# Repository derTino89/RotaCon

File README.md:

# RotaCon
 full Project with 3D-Print, PCB-Layouts, Arduino-Program etc.

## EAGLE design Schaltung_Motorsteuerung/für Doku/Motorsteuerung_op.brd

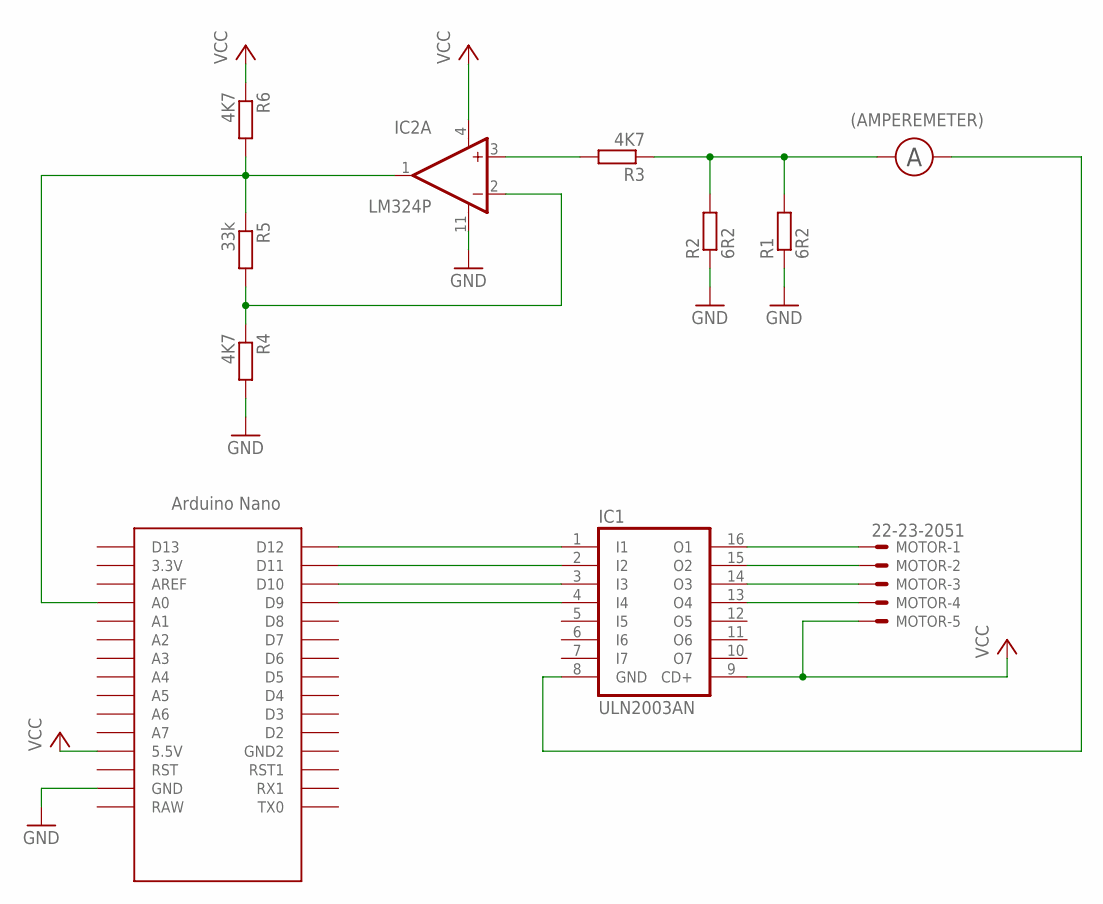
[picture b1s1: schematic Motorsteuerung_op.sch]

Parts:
IC1: ULN2003AN; DIL16
IC2: LM324P; DIL14
MOTOR: 22-23-2051
R1, R2: 6R2; 0207/10
R3, R4, R6: 4K7; 0207/10
R5: 33k; 0207/10
U$1: NANO

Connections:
GND: IC2.11 (V-), R1.1, R2.1, R4.2, U$1.GND
unnamed: IC1.16 (O1), MOTOR.1
unnamed: IC1.1 (I1), U$1.D12
unnamed: IC1.2 (I2), U$1.D11
unnamed: IC1.3 (I3), U$1.D10
unnamed: IC1.4 (I4), U$1.D9
unnamed: IC1.15 (O2), MOTOR.2
unnamed: IC1.14 (O3), MOTOR.3
unnamed: IC1.13 (O4), MOTOR.4
unnamed: R1.2, R2.2, R3.1
unnamed: IC2.3 (+IN), R3.2
unnamed: IC2.1 (OUT), R5.1, R6.2, U$1.A0
unnamed: IC2.2 (-IN), R4.1, R5.2
VCC: IC1.9 (CD+), IC2.4 (V+), MOTOR.5, R6.1, U$1.5V (5.5V)

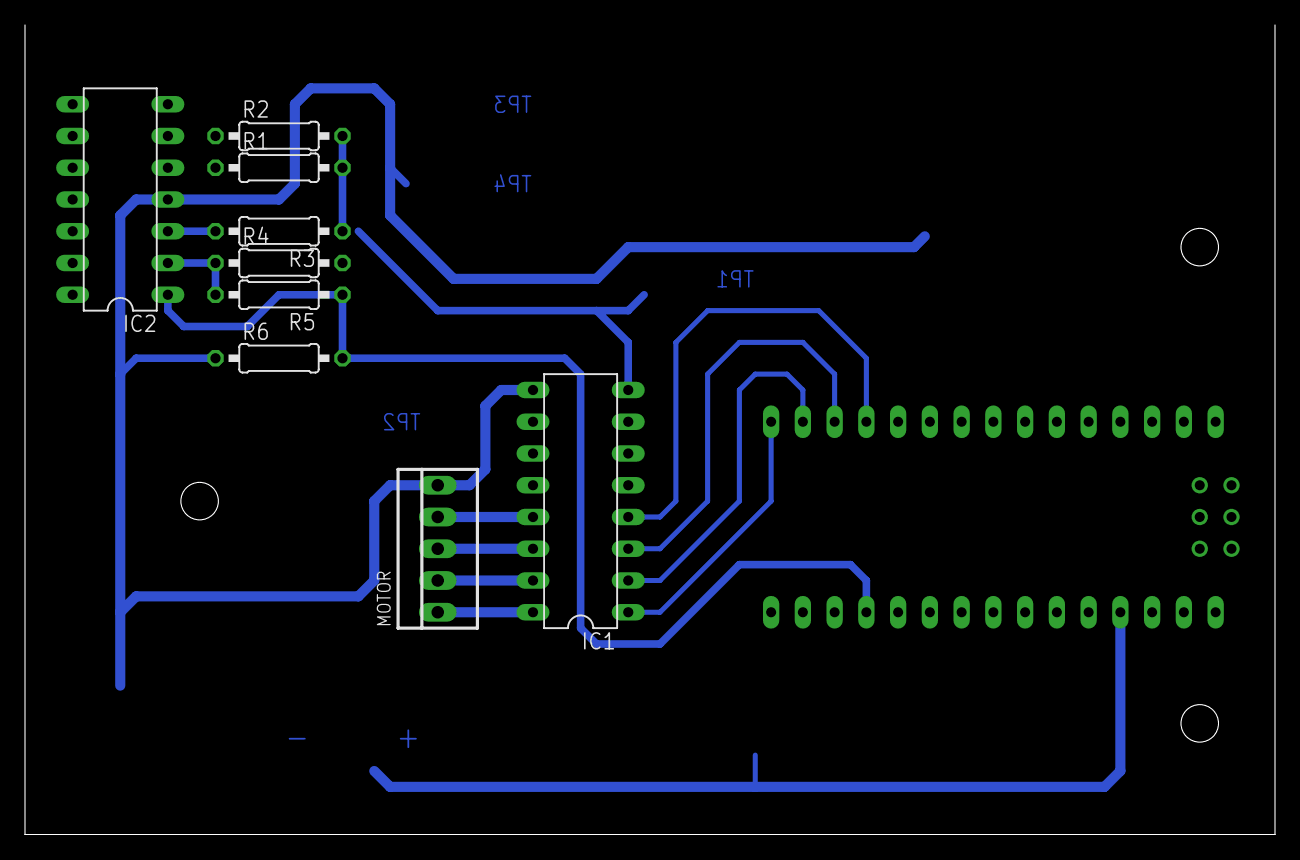
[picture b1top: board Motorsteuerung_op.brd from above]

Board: 2 copper layers, 100.0 x 64.8 mm, 10 parts (0 on the bottom side), 14 nets.

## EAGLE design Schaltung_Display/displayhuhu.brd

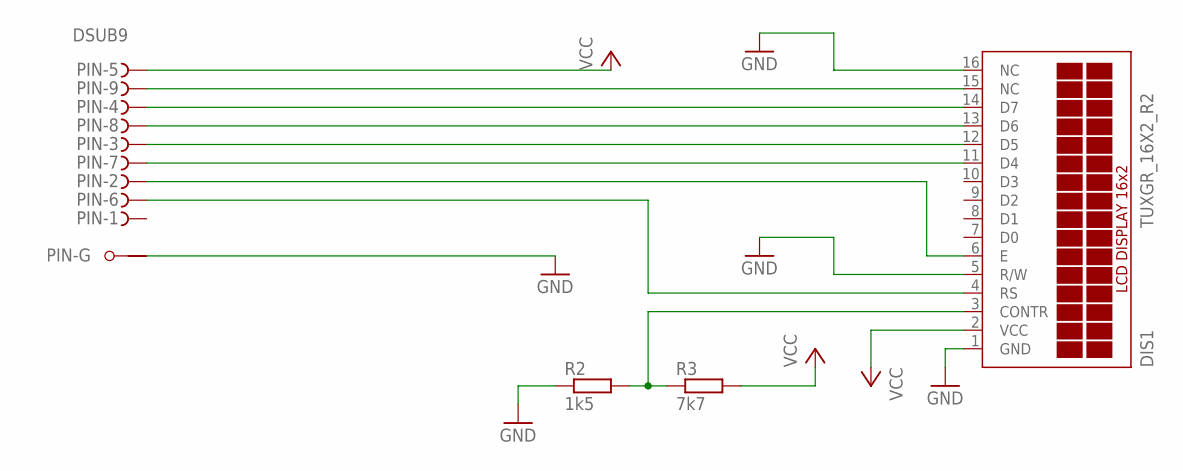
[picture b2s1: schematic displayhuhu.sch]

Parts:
DIS1: TUXGR_16X2_R2
PIN: DSUB9; F09HP
R2: 1k5; 0207/10
R3: 7k7; 0207/10

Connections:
GND: DIS1.1 (GND), DIS1.5 (R/W), DIS1.16 (NC), PIN.G1, R2.1
unnamed: DIS1.6 (E), PIN.2 (F)
unnamed: DIS1.11 (D4), PIN.7 (F)
unnamed: DIS1.12 (D5), PIN.3 (F)
unnamed: DIS1.13 (D6), PIN.8 (F)
unnamed: DIS1.14 (D7), PIN.4 (F)
unnamed: DIS1.15 (NC), PIN.9 (F)
unnamed: DIS1.4 (RS), PIN.6 (F)
unnamed: DIS1.3 (CONTR), R2.2, R3.1
VCC: DIS1.2 (VCC), PIN.5 (F), R3.2

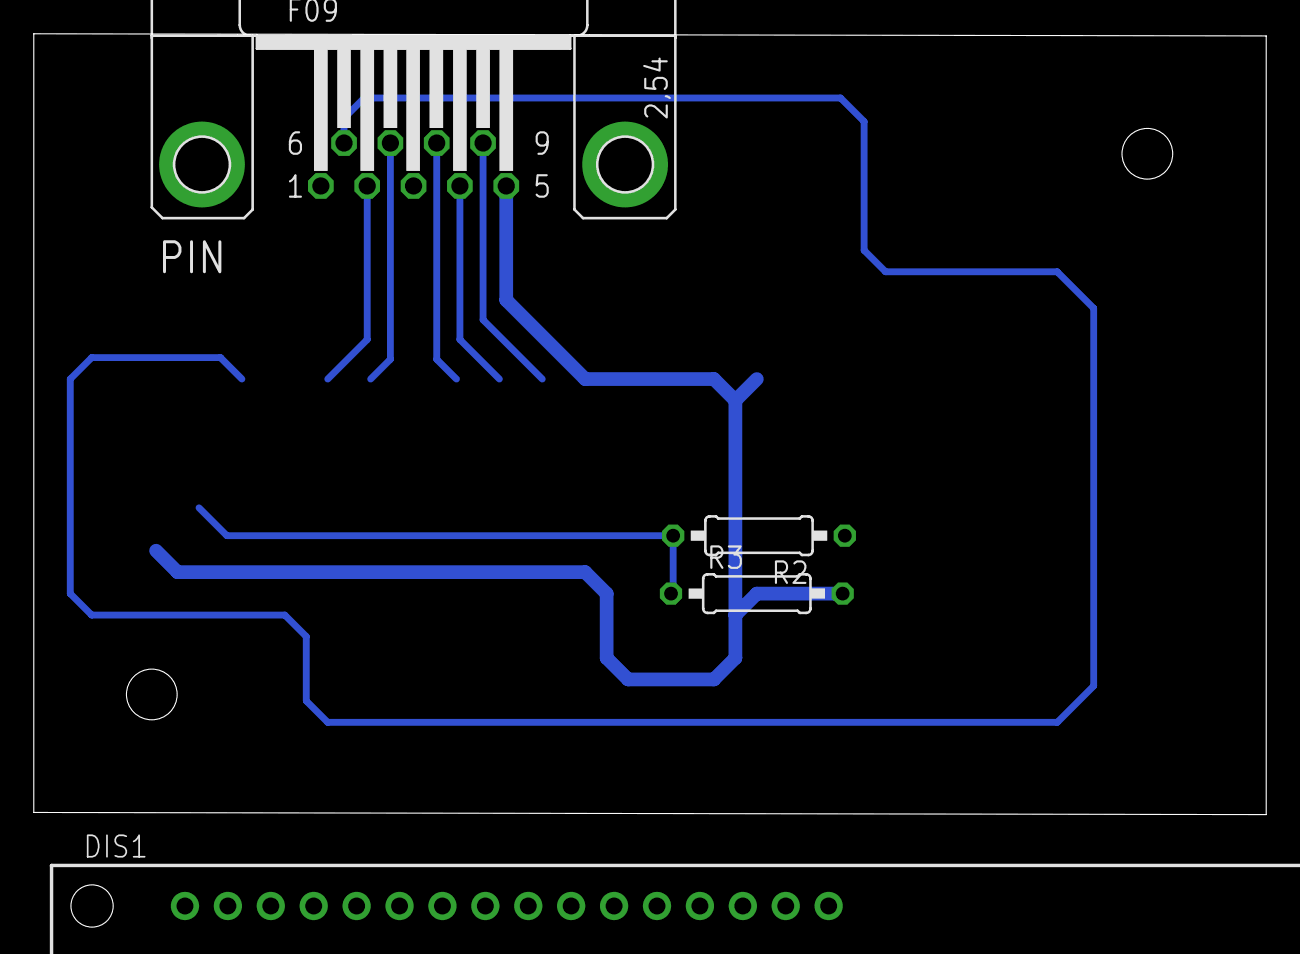
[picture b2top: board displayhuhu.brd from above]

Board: 2 copper layers, 72.9 x 46.2 mm, 4 parts (0 on the bottom side), 10 nets.

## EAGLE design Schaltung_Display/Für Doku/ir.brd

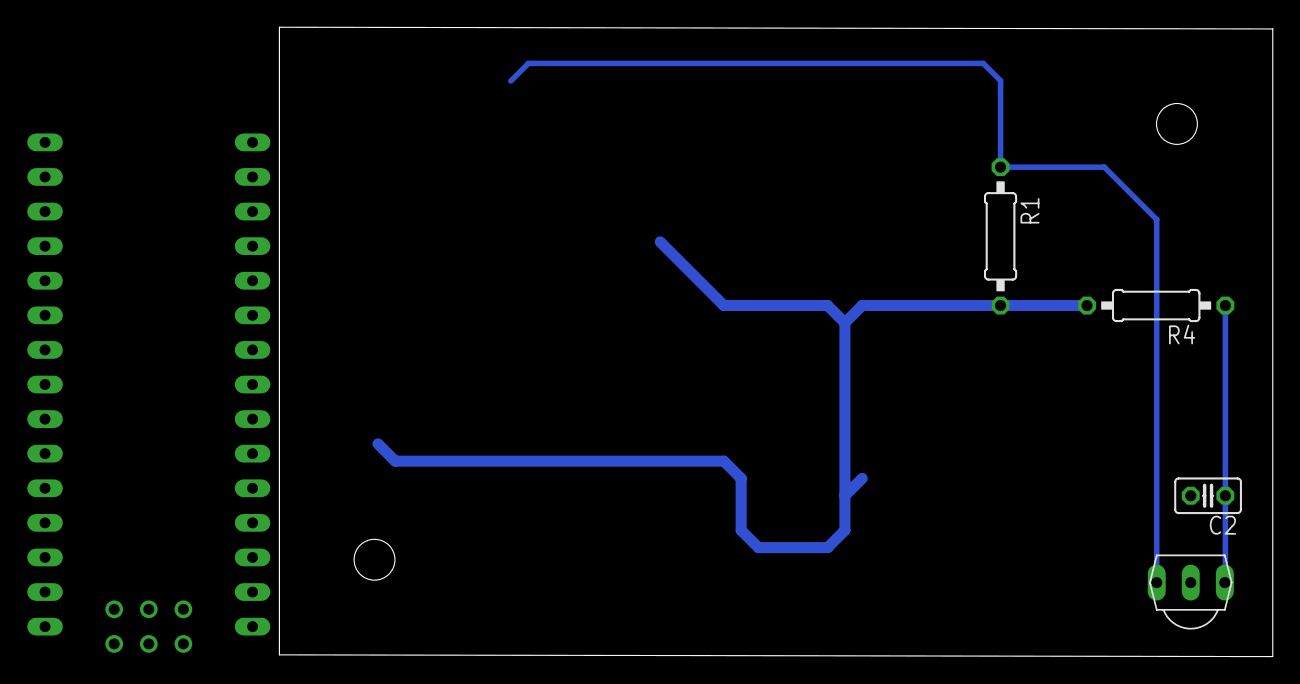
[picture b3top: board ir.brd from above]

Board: 2 copper layers, 72.9 x 46.2 mm, 5 parts (0 on the bottom side), 4 nets.

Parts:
C2: 100nF; C025-025X050
R1: 10k; 0207/10
R4: 10R; 0207/10
U$1: TSOP4838; TSOP18XX
U$2: NANO

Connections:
GND: C2.2, U$1.GND
unnamed: R1.1, U$1.OUT, U$2.A5
unnamed: C2.1, R4.1, U$1.VCC
VCC: R1.2, R4.2

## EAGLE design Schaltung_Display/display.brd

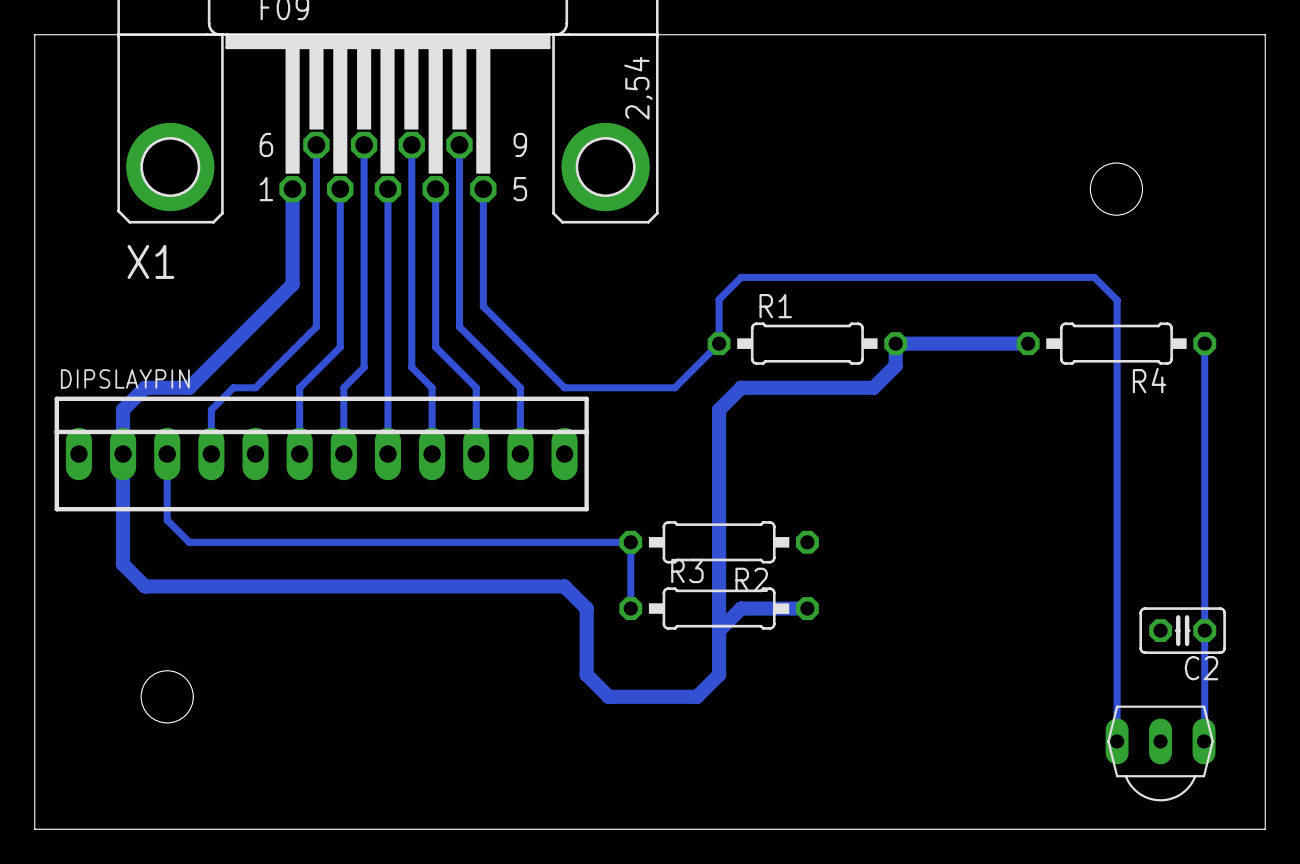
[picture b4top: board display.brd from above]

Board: 2 copper layers, 70.8 x 45.7 mm, 8 parts (0 on the bottom side), 12 nets.

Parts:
C2: 100nF; C025-025X050
DIPSLAYPIN: 22-23-2121
R1: 10k; 0207/10
R2: 1k5; 0207/10
R3: 7k7; 0207/10
R4: 10R; 0207/10
U$1: TSOP4838; TSOP18XX
X1: DSUB9; F09HP

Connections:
GND: C2.2, DIPSLAYPIN.1, DIPSLAYPIN.5, DIPSLAYPIN.12, R2.1, U$1.GND, X1.G1
unnamed: DIPSLAYPIN.6, X1.2
unnamed: DIPSLAYPIN.7, X1.7
unnamed: DIPSLAYPIN.8, X1.3
unnamed: DIPSLAYPIN.9, X1.8
unnamed: DIPSLAYPIN.10, X1.4
unnamed: DIPSLAYPIN.11, X1.9
unnamed: R1.1, U$1.OUT, X1.5
unnamed: DIPSLAYPIN.4, X1.6
unnamed: DIPSLAYPIN.3, R2.2, R3.1
unnamed: C2.1, R4.1, U$1.VCC
VCC: DIPSLAYPIN.2, R1.2, R3.2, R4.2, X1.1

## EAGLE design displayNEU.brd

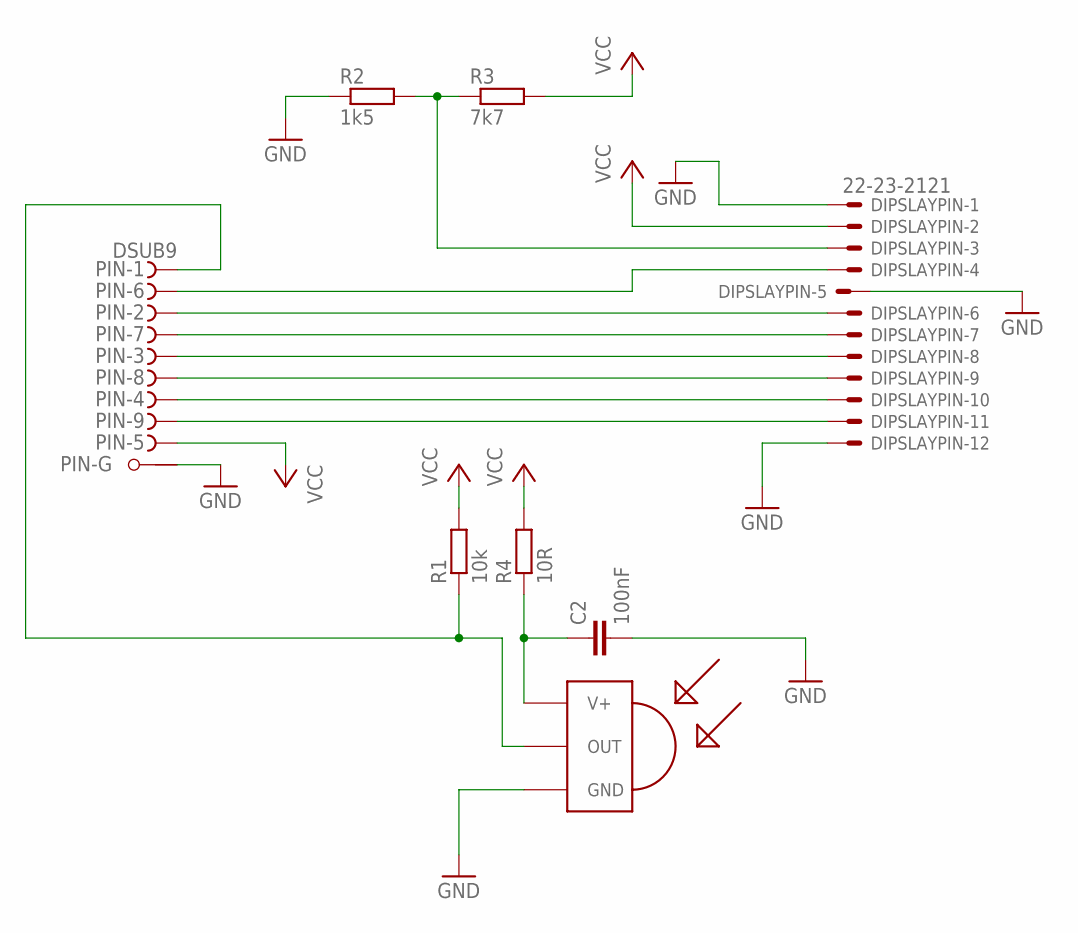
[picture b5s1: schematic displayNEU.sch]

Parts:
C2: 100nF; C025-025X050
DIPSLAYPIN: 22-23-2121
PIN: DSUB9; F09HP
R1: 10k; 0207/10
R2: 1k5; 0207/10
R3: 7k7; 0207/10
R4: 10R; 0207/10
U$1: TSOP4838; TSOP18XX

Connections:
GND: C2.2, DIPSLAYPIN.1, DIPSLAYPIN.5, DIPSLAYPIN.12, PIN.G1, R2.1, U$1.GND
unnamed: DIPSLAYPIN.6, PIN.2 (F)
unnamed: DIPSLAYPIN.7, PIN.7 (F)
unnamed: DIPSLAYPIN.8, PIN.3 (F)
unnamed: DIPSLAYPIN.9, PIN.8 (F)
unnamed: DIPSLAYPIN.10, PIN.4 (F)
unnamed: DIPSLAYPIN.11, PIN.9 (F)
unnamed: PIN.1 (F), R1.1, U$1.OUT
unnamed: DIPSLAYPIN.4, PIN.6 (F)
unnamed: DIPSLAYPIN.3, R2.2, R3.1
unnamed: C2.1, R4.1, U$1.VCC (V+)
VCC: DIPSLAYPIN.2, PIN.5 (F), R1.2, R3.2, R4.2

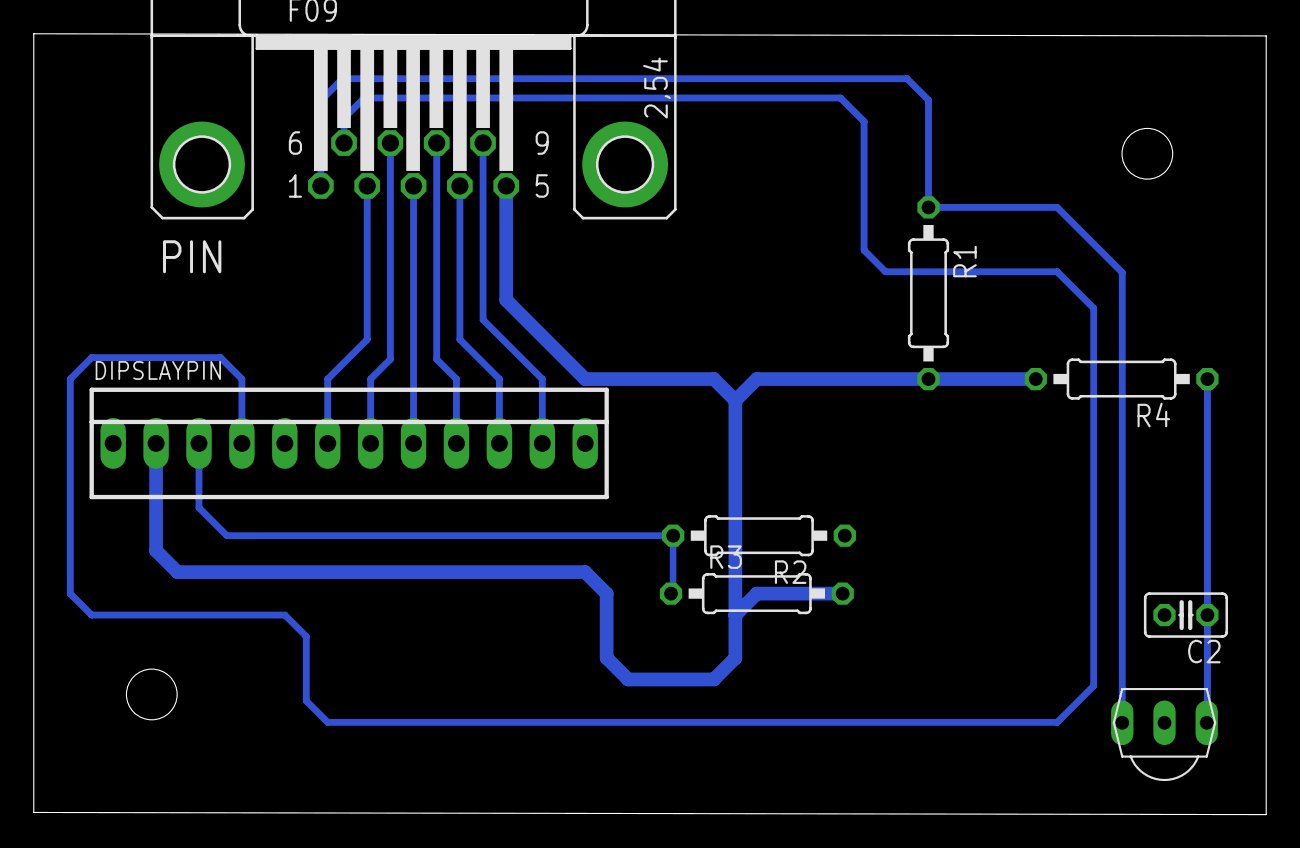
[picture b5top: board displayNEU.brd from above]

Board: 2 copper layers, 72.9 x 46.2 mm, 8 parts (0 on the bottom side), 12 nets.

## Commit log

2020-01-16 Start
2020-01-16 Doku
    implement Doku here
2020-01-16 DocumentaionDirectory added
2020-01-26 update without change
2020-02-05 Update
    -function to move one step changed
    -messuring changed
2020-02-06 Update 1
    simple start in the Theory-Part
2020-02-10 Update 2
    added some parts in chapter 2 + acronyms
2020-02-13 Update 3
    Added electric cirquit diagrams,
    pin-routing-table,
    description of IR-Module
2020-02-15 Update 4
    added more parts
2020-02-19 Update 5
    added Bib-Library, Casings an many new parts to the documentation
2020-02-22 Update 6
    more addidtions to the documentation
2020-02-27 Update 7
    Changed format in different parts. (f.e. right border of ducument to 2.5cm)
2020-03-01 Update 8
    Included attachments (chapter 5)
    corrections in chapter 3
2020-03-04 Update 9
    completed version
2020-03-04 Update 10
    small corrections
2020-03-05 Update 11
    Documentation final version
2020-03-05 Update 12
    small addition in documentation

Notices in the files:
parts and their libraries:
luani_docuSymbol: CC-BY-SA 3.0
